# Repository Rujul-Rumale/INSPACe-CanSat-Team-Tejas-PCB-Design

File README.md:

# Tejas CanSat — Onboard Computer (OBC) PCB

Carrier board for our INSPACe CanSat ("Tejas") — Teensy 4.1, XBee radio, and a full
sensor suite (BNO055, BME688, DPS310, INA260, MICS5524) with dual buck regulators,
servo/ESC headers, and buzzer on a ~102×102 mm 2-layer board.

Designed by me (**Rujul Rumale**) in KiCad, Oct 2025 — schematic, layout, and Gerber
release. I also put together the data-processing section of our PFR deck.

| Top | Bottom |
|---|---|
|  |  |

*Renders: KiCad raytracer. The custom module 3D bodies use absolute paths from my
old workstation, so modules show as footprints here — geometry and Gerbers are unaffected.*

## Photos — fabbed and assembled

The real thing: blue soldermask, fully populated and wired.

| Bare fab — top | Bare fab — bottom |
|---|---|
|  |  |

| 3D preview with modules — top | 3D preview with modules — bottom |
|---|---|
|  |  |

## Board at a glance

- **Size:** 101.9 × 101.9 mm, 1.6 mm stackup, 2-layer (`docs/board-stats.rpt`)
- **Parts:** 41 BOM lines (`docs/bom.csv`) — Teensy 4.1, XBee, BNO055, BME280/BME688,
  MICS5524, DPS310, INA260, 2× buck (MINI560/MP1584), XT30, coin-cell retainer,
  servo/ESC headers
- **Copper:** 0.3 mm min track, 0.2 mm clearance, 38 vias, 199 pads
- **Fun detail:** the bottom silkscreen carries `TEAM TEJAS`, a QR code, and our
  team names — see `docs/renders/gerber-compare/v4-bottom.png`

## What's in here

| Path | What it is |
|---|---|
| `hardware/` | KiCad project — schematic (rev 2), layout, project settings. Opens in KiCad 9.0+ |
| `manufacturing/gerber-V4/` | The Gerber release we sent to fab (12 files, Oct 9) |
| `manufacturing/gerber-V3/` | Same design, plotted ~90 s earlier — kept for reference |
| `docs/renders/` | 3D PNGs, 2D front/back SVGs, schematic PDF, V3-vs-V4 Gerber comparisons |
| `docs/photos/` | Fab + assembly photos and module-fitted 3D previews |
| `docs/bom.csv` | Bill of materials, exported from the schematic |
| `docs/board-stats.rpt` | Layer / component / drill statistics |
| `docs/Tejas.pdf`, `docs/Tejas_Sch.pdf` | Board and schematic exports from the project |
| `libs/` | The symbol/footprint/3D libraries this board uses — see `libs/README.md` |
| `history/` | 25 KiCad auto-backup snapshots (Oct 4–18) plus the earliest Oct 3 schematic draft |
| `DESIGN_NOTES.md` | How the design evolved, and revision status |

## My work on this project

This was a team build. My contributions were the complete PCB — schematic,
footprints, layout, DRC, and the Gerber release — plus the data-processing
section of our PFR presentation. I also led the mechanical structure (3D
modeled in Autodesk Fusion with a teammate's help, 3D printed in ABS).
My teammates handled flight software, the ground-station GUI, MCP server,
and telemetry operations.

## Revision status

`manufacturing/gerber-V4/` is the release we flew. The working board file in
`hardware/` has a later board-outline experiment (stepped/notched edge, mounting
holes removed) that we decided not to go with — details in `DESIGN_NOTES.md`.
So if you want to build this, use the V4 Gerbers.

## Known issue → next rev

- **XBee mounting holes too small.** They're currently drawn at 0.5 mm drill
  (`libs/XB24CDMPIT-001/DIP-20.kicad_mod`) with no clearance tolerance, so the
  module/header wouldn't seat. Next revision needs these holes enlarged.
  Everything else on the fabbed board checked out.

## Reuse

Hardware is shared under the **CERN Open Hardware Licence v2 (Strongly
Reciprocal)** — see `LICENSE`. Docs/images are CC-BY-4.0.

SPDX: `SPDX-License-Identifier: CERN-OHL-S-2.0`

---

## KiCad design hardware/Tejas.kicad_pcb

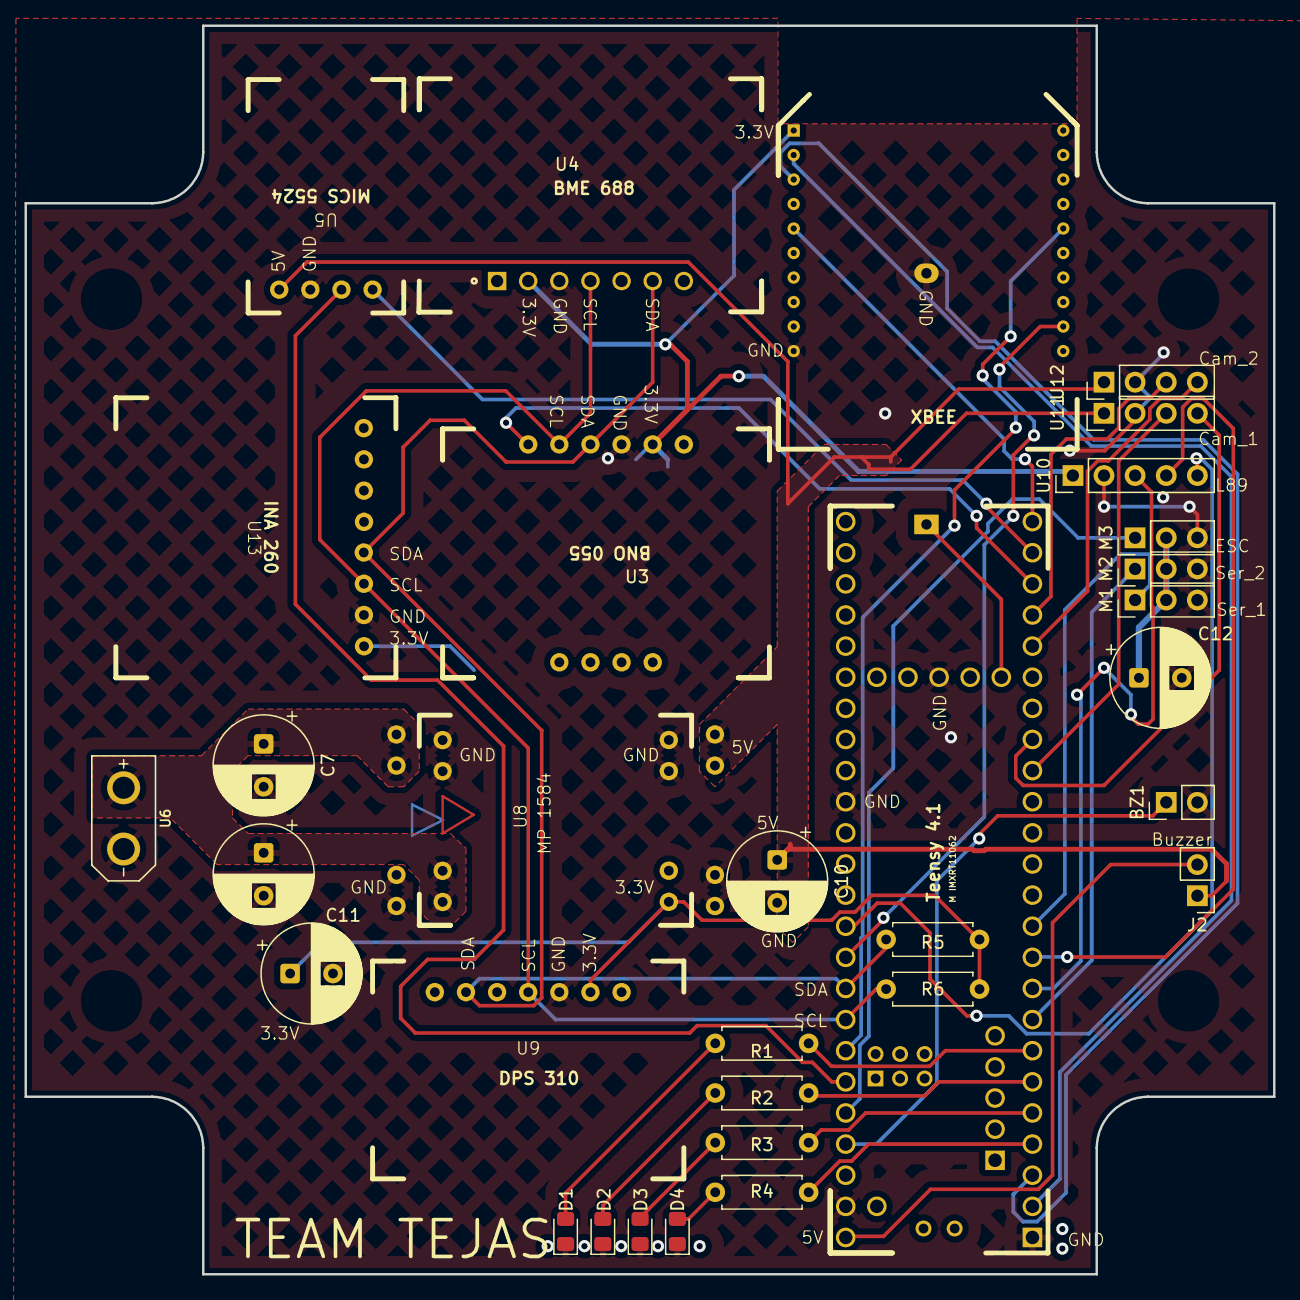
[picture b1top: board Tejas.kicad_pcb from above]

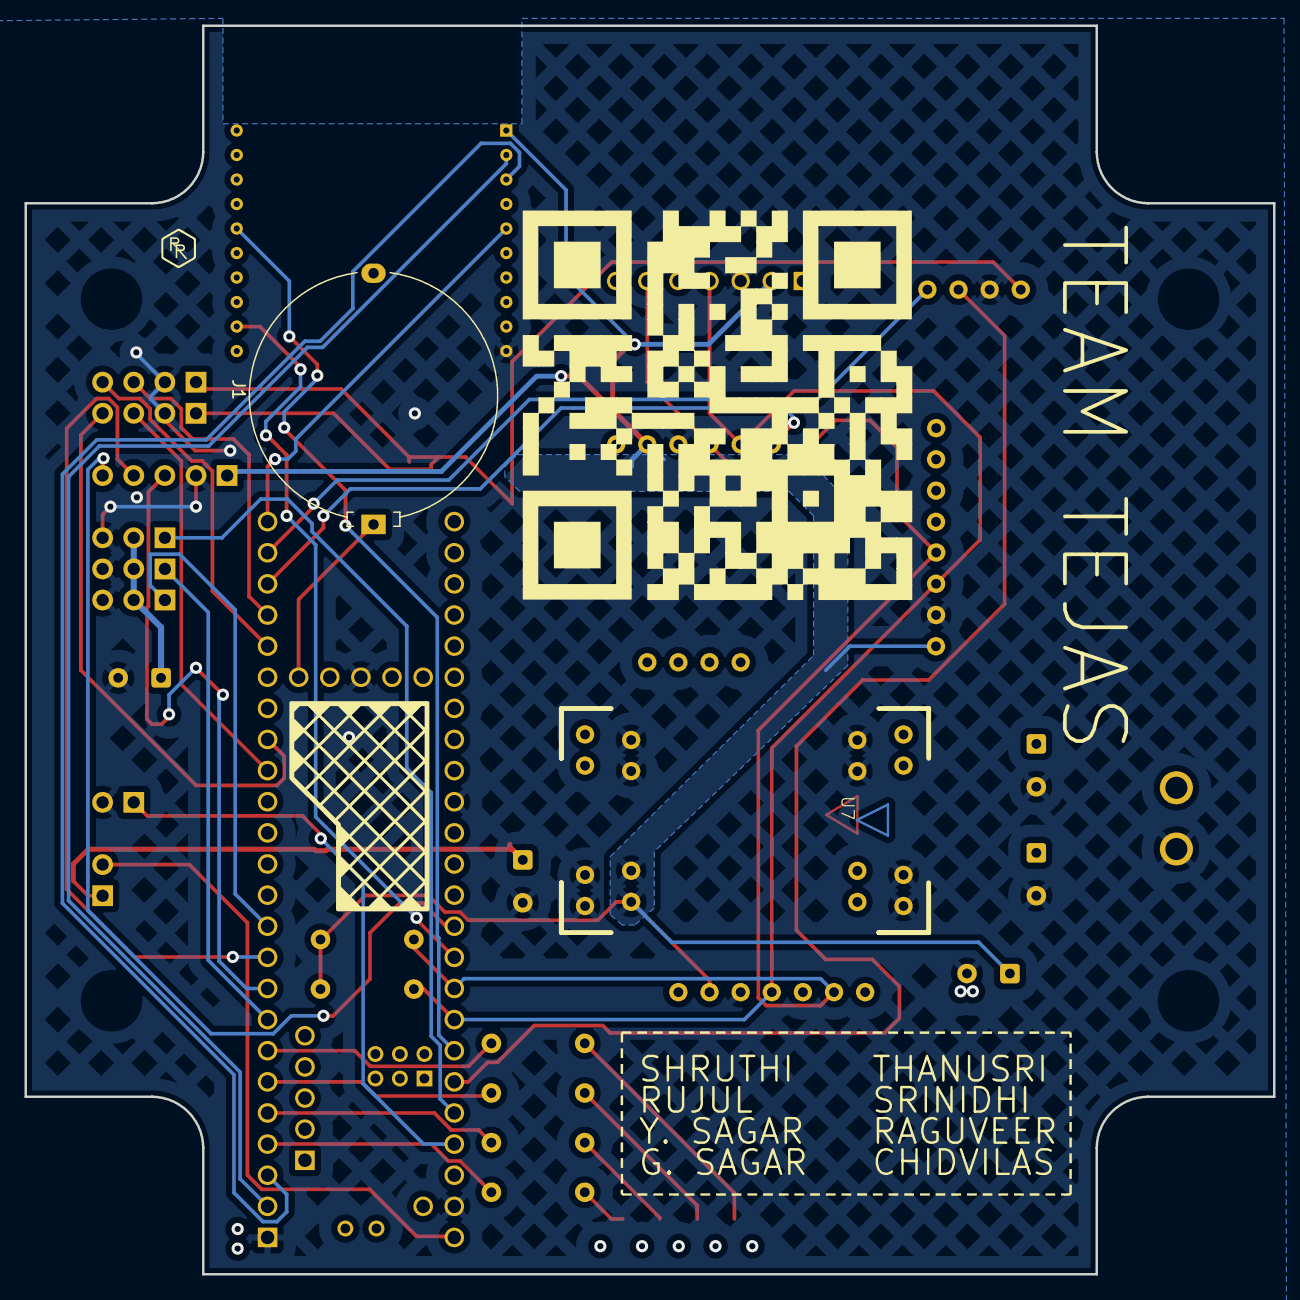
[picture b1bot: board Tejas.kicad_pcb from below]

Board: 2 copper layers, 101.9 x 101.9 mm, 34 parts (2 on the bottom side), 36 nets.

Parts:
BZ1: Buzzer; PinHeader_1x02_P2.54mm_Vertical
C7, C9, C10, C11, C12: C_Polarized; CP_Radial_D8.0mm_P3.50mm
D1, D2, D3, D4: LED; LED_0805_2012Metric_Pad1.15x1.40mm_HandSolder
J1: S8421-45R; Battery_Panasonic_CR2032-HFN_Horizontal_CircularHoles
J2: Conn_01x02_Pin; PinHeader_1x02_P2.54mm_Vertical
M1, M2, M3: Motor_Servo; PinHeader_1x03_P2.54mm_Vertical
R1, R2, R3, R4, R5, R6: R; R_Axial_DIN0207_L6.3mm_D2.5mm_P7.62mm_Horizontal
U1: Teensy4.1; Teensy41
U2: XB24-ASI-001; DIP-20
U3: BNO055; MODULE_2472
U4: BME280; MODULE_2652
U5: MICS_5524; MICS 5524
U6: XT30UPB-M
U7: BUCK_5A; MINI560
U8: BUCK_5A; MP1284
U9: DPS310; DPS 310
U10: L89; PinHeader_1x05_P2.54mm_Vertical
U11, U12: ESP; PinHeader_1x04_P2.54mm_Vertical
U13: INA260; INA_260

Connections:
3.3V: C11.1, R5.2, R6.2, U2.1, U3.2 (3VO), U4.2 (3VO), U8.3 (VOUT+), U9.2 (3V0), U10.1 (VCC), U13.1 (vcc)
5V: C10.1, J2.1, U5.1 (VDD), U7.3 (VOUT+), U11.1 (5V), U12.1 (5V)
11.1+: C7.1, C9.1, U6.P$1 (+), U7.1 (VIN+), U8.1 (VIN+)
11.1-: BZ1.2 (-), C7.2, C9.2, C10.2, C11.2, C12.2, D1.1 (K), D2.1 (K), D3.1 (K), D4.1 (K), J1.2, M1.3 (-), M2.3 (-), M3.3 (-), U1.1 (GND), U1.34 (GND), U1.47 (GND), U1.52 (GND), U2.10, U3.3 (GND), U4.3 (GND), U5.2 (GND), U6.P$2 (-), U7.2 (VIN-), U7.4 (VOUT-), U8.2 (VIN-), U8.4 (VOUT-), U9.3 (GND), U10.2 (GND), U11.2 (GND), U12.2 (GND), U13.2 (gnd)
/A6: U1.43 (21_A7_RX5_BCLK1), U5.3 (A0)
/Buzz: BZ1.1 (+), U1.45 (23_A9_CRX1_MCLK1)
/EN: U1.23 (31_CTX3), U5.4 (EN)
/ESC: M3.1 (PWM), U1.44 (22_A8_CTX1)
/LED1: R1.2, U1.7 (5_IN2)
/LED2: R2.2, U1.6 (4_BCLK2)
/LED3: R3.2, U1.5 (3_LRCLK2)
/LED4: R4.2, U1.4 (2_OUT2)
/RST1: U1.22 (30_CRX3), U3.6 (RST)
/RST2: U1.24 (32_OUT1B), U2.5
/RST3: U1.38 (16_A2_RX4_SCL1), U10.5 (RST)
/RX1: U1.2 (0_RX1_CRX2_CS1), U2.2
/Servo_1: M1.1 (PWM), U1.11 (9_OUT1C)
/Servo_2: M2.1 (PWM), U1.8 (6_OUT1D)
/TX1: U1.3 (1_TX1_CTX2_MISO1), U2.3
unnamed: D1.2 (A), R1.1
unnamed: D2.2 (A), R2.1
unnamed: D3.2 (A), R3.1
unnamed: D4.2 (A), R4.1
unnamed: J2.2, U1.48 (VIN)
unnamed: C12.1, M1.2 (+), M2.2 (+), M3.2 (+)
unnamed: U1.9 (7_RX2_OUT1A), U10.3 (TX)
unnamed: U1.10 (8_TX2_IN1), U10.4 (RX)
unnamed: U1.39 (17_A3_TX4_SDA1), U2.12
unnamed: U1.42 (20_A6_TX5_LRCLK1), U2.16
unnamed: U1.16 (24_A10_TX6_SCL2), U11.3 (RX)
unnamed: U1.17 (25_A11_RX6_SDA2), U11.4 (TX)
unnamed: U1.20 (28_RX7), U12.4 (TX)
unnamed: U1.21 (29_TX7), U12.3 (RX)
unnamed: J1.1, U1.50 (VBAT)
SCL: R6.1, U1.41 (19_A5_SCL), U3.5 (SCL), U4.4 (SCK), U9.4 (SCL), U13.3 (scl)
SDA: R5.1, U1.40 (18_A4_SDA), U3.4 (SDA), U4.6 (SDI), U9.6 (SD1), U13.4 (sda)
